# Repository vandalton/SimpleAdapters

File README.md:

# SimpleAdapters

## Description

Code for simple joysticks, keyboards adapters.

## Remarks

Use it at your own risk.

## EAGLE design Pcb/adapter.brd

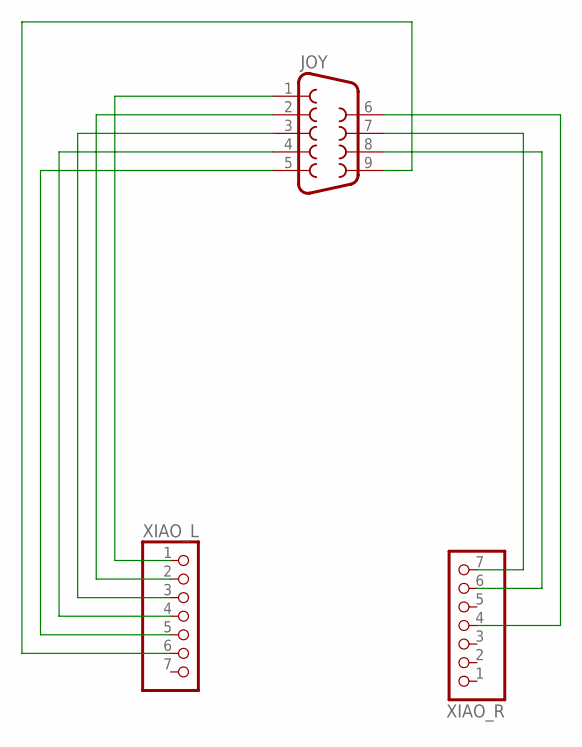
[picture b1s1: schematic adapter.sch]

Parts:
JOY: F09D
XIAO_L: PINHD-1X7; 1X07
XIAO_R: PINHD-1X7; 1X07

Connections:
unnamed: JOY.8, XIAO_R.6
unnamed: JOY.1, XIAO_L.1
unnamed: JOY.7, XIAO_R.7
unnamed: JOY.2, XIAO_L.2
unnamed: JOY.3, XIAO_L.3
unnamed: JOY.4, XIAO_L.4
unnamed: JOY.5, XIAO_L.5
unnamed: JOY.9, XIAO_L.6
unnamed: JOY.6, XIAO_R.4

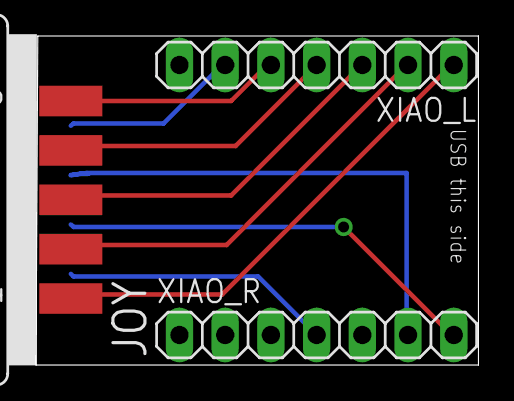
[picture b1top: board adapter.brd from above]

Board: 2 copper layers, 24.6 x 18.3 mm, 3 parts (0 on the bottom side), 9 nets.

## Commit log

2021-08-23 Add keyboard-as-joystick adapter for Amiga
2022-04-03 Add ps4 and usb mouse support
2022-04-04 Undo some experiments
2022-04-09 Introduce scaling for mice with high dpi
2022-08-16 Add switchable scaling
2022-08-16 Add pcb design
2023-04-07 Add nes to db9
2023-04-08 Add db9 to usb adapter code
2024-02-03 Add usb-keyboard-as-two-joysticks and usb-keyboard-as-atari2600-keyboard adapters
2024-02-27 Add new adapters - some WIP
2024-02-27 Atari 2600 Midi adapter WIP
2024-02-29 Modify Atari 2600 Midi adapter
2024-02-29 Update Atari 2600 Midi adapter
2024-03-29 Add Atari 2600 Midi adapter
2024-08-28 Add Xbox adapter
2024-11-26 Xbox controller can act as mouse
